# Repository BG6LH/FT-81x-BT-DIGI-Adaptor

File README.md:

Since 2025/06/11 

---
English | [简体中文](./README.zh-CN.md)

# A PCB Design of Bluetooth DIGI Adaptor for Yaesu FT-817/818 Series Transceivers

> **NOTE: This Design is still a Work in Progress. Schematic, PCB, and other stuff might change!**

## Table of Contents
- [Update](#update)
- [Important](#important)
- [Background](#background)
- [Design](#design)
- [Code Repositories](#code-repositories)
- [Configuration of JDY-67](#configuration-of-JDY-67)
- [3D Printed Protect Cover](#3d-printed-protect-cover)
- [Related Efforts](#related-efforts)
- [Contributing](#contributing)
- [Maintainers](#maintainers)
- [License](#license)

## Update

### Updated in 20240120

**Important:** Fixed the 20230609 version‘s power supply part's resistor value.

Right Choice should be this:
* R10 = 100KΩ
* R11 = 100KΩ
* R12 = 1KΩ
* R6 = 10Ω

The LM1117-3.3V is also a good choice.
All about that can work well at once!

The PCB design is as same as 20230609, so the old Gerber files are still work.

A 3D printed Cover has published:

[https://www.thingiverse.com/thing:6116435](https://www.thingiverse.com/thing:6116435)

### Updated in 20230609 

**Important:** The 20230608 version‘s symbols and footprints of Q1, Q2 are wrong. Please use updated in 20230609.

1. Update LDO LM1117-3.3V to 5V, to provide a constant power for the Bluetooth module;
2. Removed the Zener, and updated R6 to 150Ω, which is close to the ideal value;
3. Added power off circuit.
4. Replace VR with fixed resistor and optimize the circuit.
5. Updated some symbols and footprints.

### Updated in 20230527

The version 20230522‘s MD6 and MD8 sockets footprints were forgot to be grounded, if you has printed the PCB, you can scrape the green oil next to the shell's big pin, and then solder them together. It will as good as this version 20230527.

20230527's update includes:
1. Modified the symbols and footprints design of MD-6 and MD8 sockets, added pin 9, and grounded. Ensure that will not lost ground when updating from schematic.
2. The power divider resistor R6 is updated to 270Ω, which is close to the ideal value;
3. Added project's kicad symbols and footprints library sharing.

### Updated in 20230522
1. Add 6.2V zener for pre-conditioning before LM1117-3.3
2. Add attenuation network for Line->Mic
3. Add EMI inductor on TXD/RXD pins.
4. Removed TXD's LED.

## Important
1. The FT-817/818's ACC jack always has a constant voltage of 13.8V, even you switched off the rig. We should ***BE VERY CAREFUL*** to avoid short-circuit the PCB and ACC jack accidentally.
2. Meanwhile, aftering installing this adaptor, it will ***ALWAYS*** consume FT-817/818's battery energy. So, A battery with a power switch is recommended. For example, The WindCamp's FT-817/818 lithium battery.
3. If you would purchase a JDY-67 Bluetooth moudle, make sure the firmware version is ***Above 1.3***.

## Background
My friend BG6JJI designed a Bluetooth DIGI adaptor working for many old style TRXs with a Bluetooth, DIGI and CAT ability. He was using a Bluetooth module named JDY-67. I am not sure which manufacturer made the JDY-67. But it's really inexpensive and really works for Bluetooth Audio, and SPP in same time.

So, I pick up an old PCB design for my FT-818. It was design for FT8 cable connecting at very beginning. However, with JDY-67, It should works for Bluetooh/DIGI/CAT. I'd measured the DATA and ACC jacks on FT-818's rear panel, And refering to the FT-817ND's Service Manual, I think the Yaesu's PCB maybe design in a 0.635mm/0.025inch grid. Under this assumption, I'd drawn a PCB that could cover most of the FT-817 rear panel, and perfectly matched all the screw holes, jacks....precisely!!! It looks like a underwear(under-bottom-hardware), right?

Although FT-817/818 has been discontinued, I still love this twenty years selling product. Now, I would like to share this PCB desgin to all HAM communities, If you wanna make your design, you can make any modify from it.

## Design
This PCB was design by KiCad 7.0
In the Layer User.Drawings and User.Comments, there are some information of measurement.
In the Layer User.1~4, there are approximate FT-817/818's panel sketch for comparison.

## Code Repositories

- Github [https://github.com/BG6LH/FT-81x-BT-DIGI-Adaptor](https://github.com/BG6LH/FT-81x-BT-DIGI-Adaptor)
- Gitee [https://gitee.com/bg6lh/FT-81x-BT-DIGI-Adaptor](https://gitee.com/bg6lh/FT-81x-BT-DIGI-Adaptor)

## Configuration of JDY-67

Please note, the JDY-67's default BAUD is 9600bps.

Before connect the adaptor to phone or computer, there are three bluetooth configuration need to be changed. please use those serial port AT instructions:
```sh
AT+SING1\r\n
# Turn on single-ended output 

AT+ROLE0\r\n
# Turn off BLE bluetooth

AT+CALEN1\r\n
# Turn on the phone function

AT+RST\r\n
# Restart the moudule
```
Jdy-67 module serial command must be plus \r\n .

## 3D Printed Protect Cover

A 3D printed Cover has published:
[https://www.thingiverse.com/thing:6116435](https://www.thingiverse.com/thing:6116435)

## Related Efforts
- [FT8CN for Android](https://github.com/N0BOY/FT8CN) - Run FT8 natively on Android. This app works well with our Bluetooth DIGI Adaptor.

## Contributing
With special thanks to **BG6JJI, BI1EIH***. They give me many generous advice.

Let's enjoy the FT-817's last lucky underware together!!

## Maintainers
- [@BG6LH(me)](https://github.com/BG6LH)
- [@sgub(BI1EIH)](https://github.com/sgub)

## Star History

## License

This work is licensed under a
[Creative Commons Attribution-NonCommercial-ShareAlike 4.0 International (CC BY-NC-SA 4.0)][cc-by-nc-sa].

[![CC BY NC SA 4.0][cc-by-nc-sa-image]][cc-by-nc-sa]

[cc-by-nc-sa]: https://creativecommons.org/licenses/by-nc-sa/4.0/
[cc-by-nc-sa-image]: https://i.creativecommons.org/l/by-nc-sa/4.0/88x31.png

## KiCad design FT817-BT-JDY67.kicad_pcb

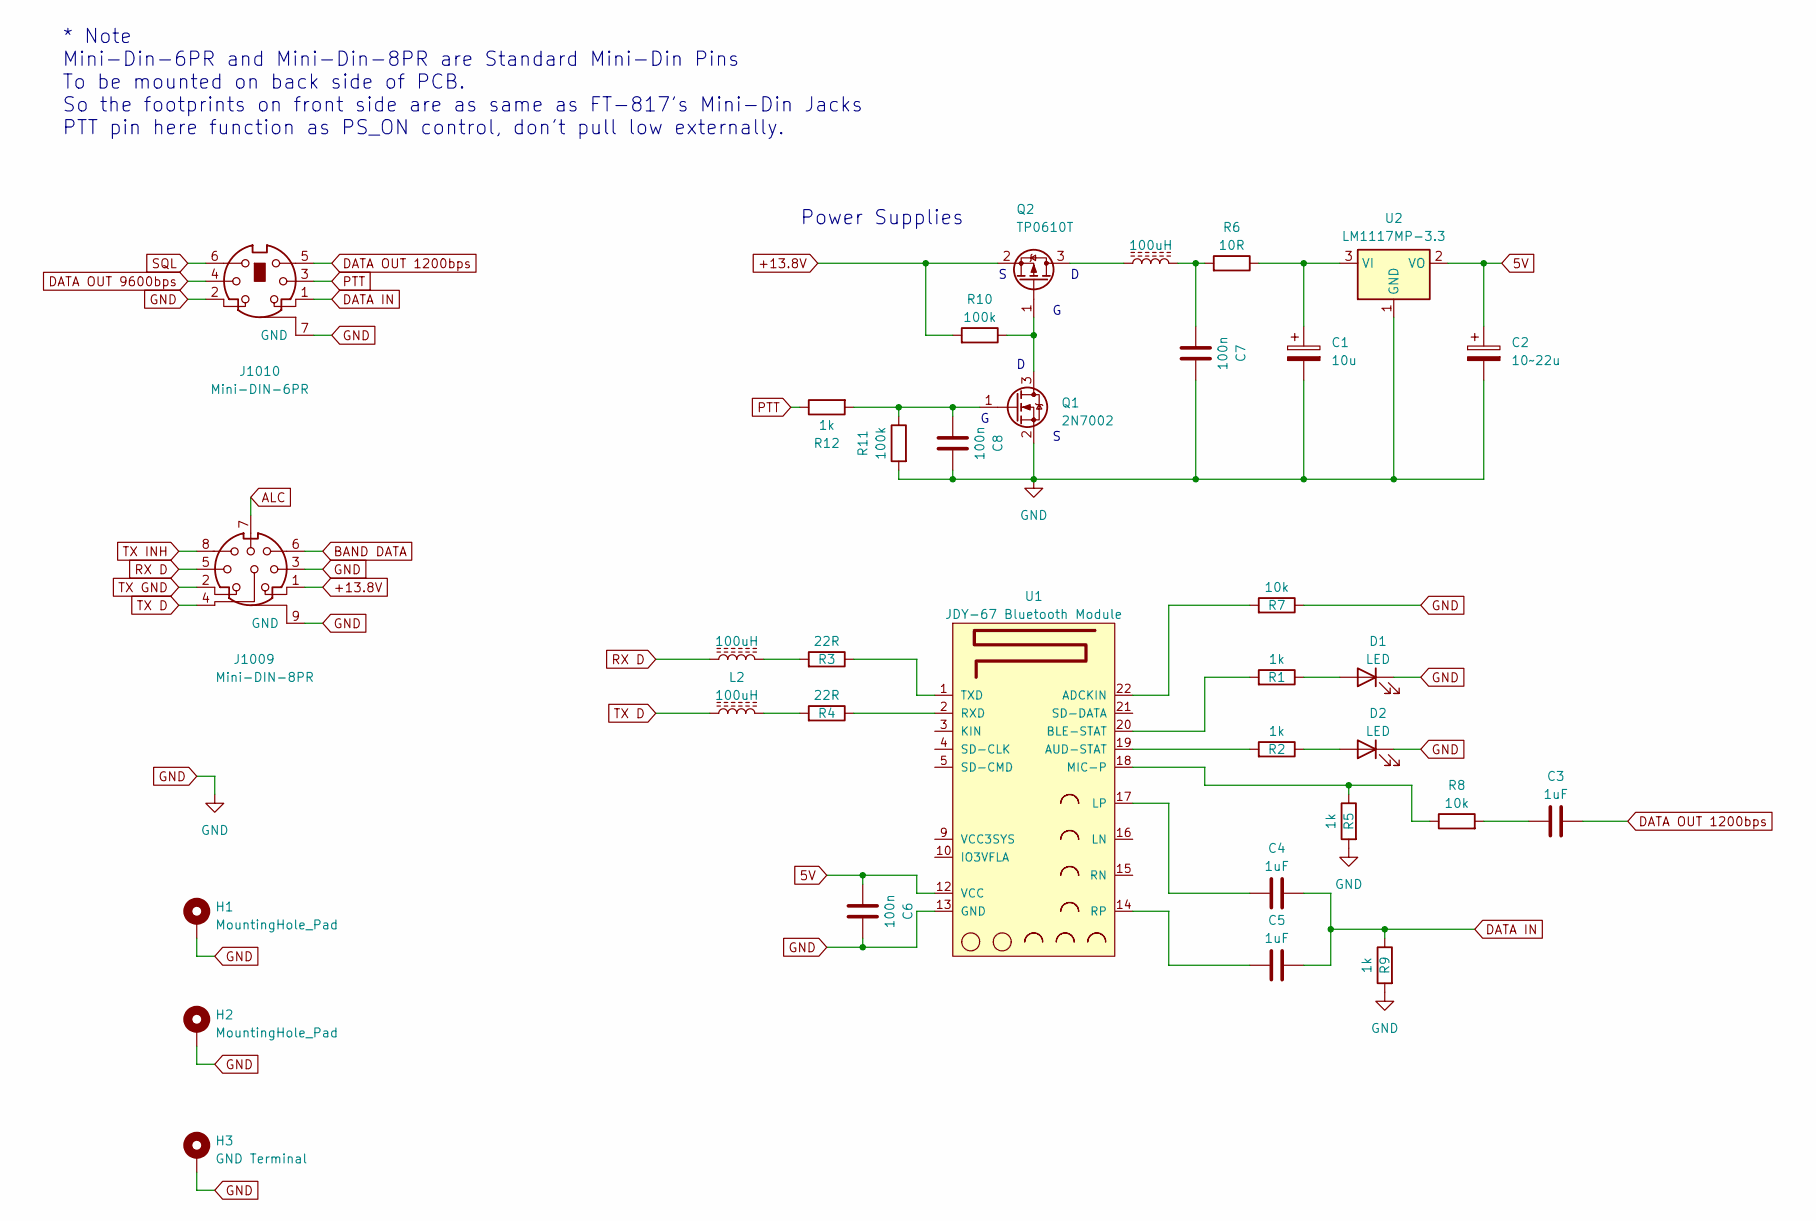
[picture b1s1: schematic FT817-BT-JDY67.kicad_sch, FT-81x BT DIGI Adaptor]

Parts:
C1: 10u; CP_EIA-3216-18_Kemet-A
C2: 10~22u; CP_EIA-3216-18_Kemet-A
C3, C4, C5: 1uF; C_0805_2012Metric
C6, C7, C8: 100n; C_0805_2012Metric
D1, D2: LED; LED_0805_2012Metric
H1, H2: MountingHole_Pad; MountingHole_2.7mm_M2.5_DIN965_Pad_TopOnly
H3: GND Terminal; FT-817_GND_terminal_8.4mm_M8_Pad_TopBottom
J1009: Mini-DIN-8PR; MD-8Pin_Reverse
J1010: Mini-DIN-6PR; MD-6Pin_Reverse
L1, L2, L3: 100uH; L_0805_2012Metric_Pad1.05x1.20mm_HandSolder
Q1: 2N7002; SOT-23
Q2: TP0610T; SOT-23
R1, R2, R5, R9, R12: 1k; R_0805_2012Metric
R3, R4: 22R; R_0805_2012Metric
R6: 10R; R_0805_2012Metric
R7, R8: 10k; R_0805_2012Metric
R10, R11: 100k; R_0805_2012Metric
U1: JDY-67 Bluetooth Module; JDY-67_Bluetooth_Module
U2: LM1117MP-3.3; SOT-223-3_TabPin2

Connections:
5V: C2.1, C6.1, U1.12 (VCC), U2.2 (VO)
+13.8V: J1009.1, Q2.2 (S), R10.2
ALC: J1009.7
BAND DATA: J1009.6
DATA IN: C4.2, C5.2, J1010.1, R9.1
DATA OUT 1200bps: C3.2, J1010.5
DATA OUT 9600bps: J1010.4
GND: C1.2, C2.2, C6.2, C7.2, C8.2, D1.1 (K), D2.1 (K), H1.1, H2.1, H3.1, J1009.3, J1009.9 (GND), J1010.2, J1010.7 (GND), Q1.2 (S), R5.2, R7.1, R9.2, R11.2, U1.13 (GND), U2.1 (GND)
unnamed: C3.1, R8.2
unnamed: C7.1, L3.2, R6.2
unnamed: D1.2 (A), R1.1
unnamed: D2.2 (A), R2.1
unnamed: L1.2, R3.2
unnamed: L2.2, R4.2
unnamed: Q1.3 (D), Q2.1 (G), R10.1
unnamed: C8.1, Q1.1 (G), R11.1, R12.2
unnamed: L3.1, Q2.3 (D)
unnamed: R7.2, U1.22 (ADCKIN)
unnamed: R2.2, U1.19 (AUD-STAT)
unnamed: R1.2, U1.20 (BLE-STAT)
unnamed: C4.1, U1.17 (LP)
unnamed: R5.1, R8.1, U1.18 (MIC-P)
unnamed: C5.1, U1.14 (RP)
unnamed: R4.1, U1.2 (RXD)
unnamed: R3.1, U1.1 (TXD)
unnamed: C1.1, R6.1, U2.3 (VI)
PTT: J1010.3, R12.1
RX D: J1009.5, L1.1
SQL: J1010.6
TX D: J1009.4, L2.1
TX GND: J1009.2
TX INH: J1009.8

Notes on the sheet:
* Note Mini-Din-6PR and Mini-Din-8PR are Standard Mini-Din Pins To be mounted on back side of PCB. So the footprints on front side are as same as FT-817's Mini-Din Jacks PTT pin here function as PS_ON control, don't pull low externally.
Power Supplies

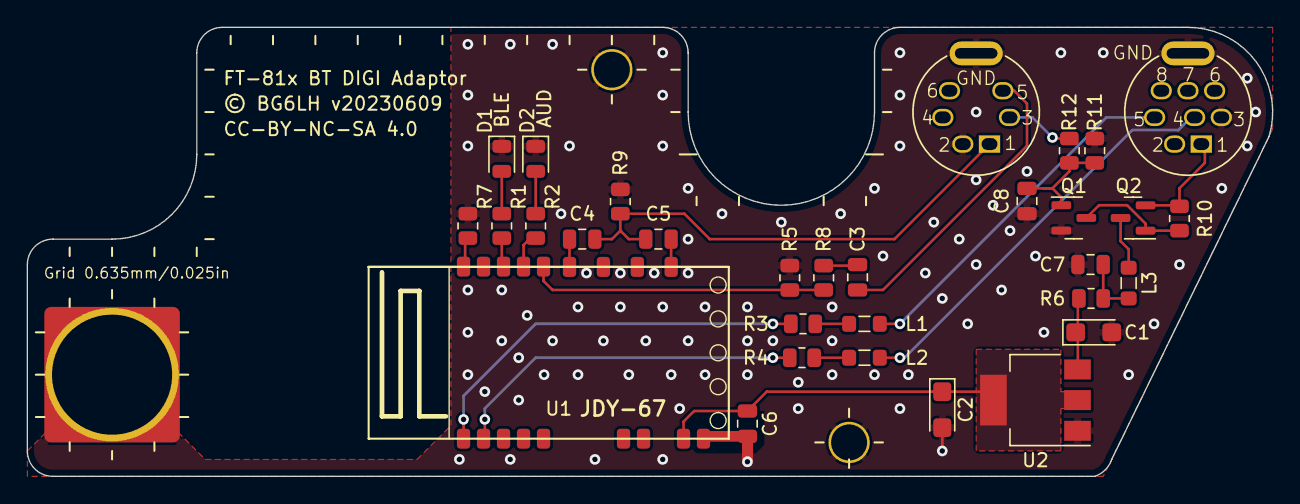
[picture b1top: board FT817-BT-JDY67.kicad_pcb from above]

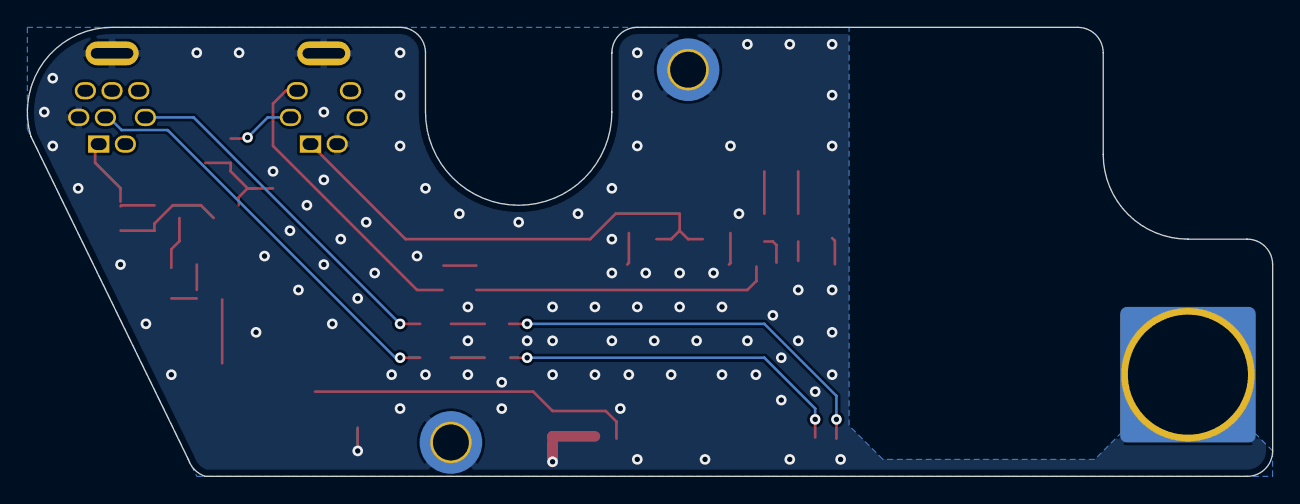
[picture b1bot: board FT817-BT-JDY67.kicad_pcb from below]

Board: 2 copper layers, 93.3 x 33.7 mm, 34 parts (2 on the bottom side), 26 nets.

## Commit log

2023-05-17 Rename LICENSE-CC-BY-NC-SA.txt to LICENSE-CC-BY-NC-SA
2023-05-17 add a 3D mod of JDY-67
    adjust the dimension
2023-05-21 1. Add 6.2V zener for pre-conditioning before LM1117-3.3 2. Add attenuation network for Line->Mic 3. Add EMI inductor on TXD/RXD pins.
2023-05-22 Reconnect D3 to RXD
2023-05-22 Updated footprint for new components.
2023-05-22 udate
2023-05-24 minimal update
2023-05-24 update pics to v20230522
2023-05-24 增加中文版说明
2023-05-27 upade
2023-05-27 update pictures to v20230527
2023-06-05 Replace VR with fixed resistor. Optimized LDO circuit.
2023-06-07 Add power shutdown circuit
2023-06-07 Remove VCC control bypass jumper
2023-06-08 pics updated
2023-06-09 Improved resolution
2023-06-09 Error founded
2023-06-09 important update
2023-06-09 Fixed 2N7002 Footprint
2023-06-13 Resources added
2024-01-20 resistors value update
    updated power supply's resistor right value.
2024-01-20 readme updated
2025-04-19 Update LICENSE
2025-04-19 Create LICENSE
2025-06-11 Badges added

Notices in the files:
FT817-BT-JDY67.kicad_pcb:
© BG6LH v20230609
